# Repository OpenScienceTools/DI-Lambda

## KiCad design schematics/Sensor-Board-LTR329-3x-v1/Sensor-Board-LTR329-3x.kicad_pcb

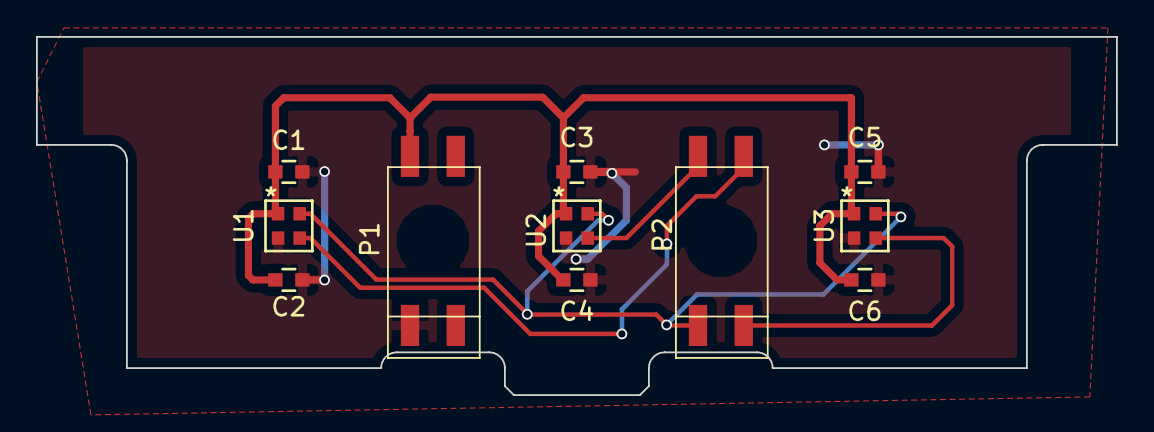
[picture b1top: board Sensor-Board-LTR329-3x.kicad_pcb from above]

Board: 2 copper layers, 60.0 x 19.9 mm, 11 parts (0 on the bottom side), 6 nets.

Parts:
C1, C3, C5: 22nF; C_0603
C2, C4, C6: 1uF; C_0603
P1, P2: CONN_02X02; SSM-102-X-DH
U1, U2, U3: LTR-329ALS-01; Liteon_ChipLED

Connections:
GND: C1.2, C2.2, C3.2, C4.2, C5.2, C6.2, P1.1, U1.2, U2.2, U3.2
SCL: P2.1, U1.4, U2.4, U3.4
SDA0: P2.4, U1.3
SDA1: P2.2, U2.3
SDA2: P2.3, U3.3
VDD: C1.1, C2.1, C3.1, C4.1, C5.1, C6.1, P1.2, U1.1, U2.1, U3.1

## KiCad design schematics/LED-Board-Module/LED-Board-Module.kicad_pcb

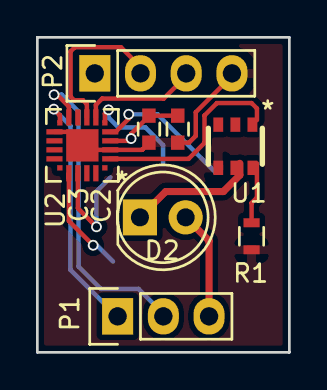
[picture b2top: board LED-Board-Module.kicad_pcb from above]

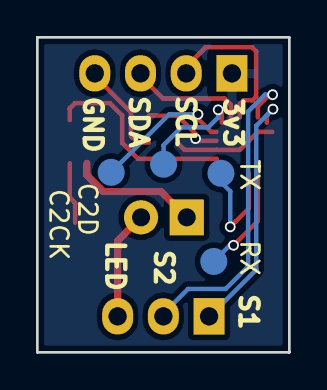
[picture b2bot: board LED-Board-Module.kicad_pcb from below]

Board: 2 copper layers, 14.0 x 17.5 mm, 12 parts (4 on the bottom side), 14 nets.

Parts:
C2: 1uF; C_0603
C3: 100nF; C_0603
D2: LED; LED-5MM
P1: CONN_01X03; Pin_Header_Straight_1x03
P2: CONN_01X04; Pin_Header_Straight_1x04
R1: 96R; R_0603
U1: BCR42XU; SOT26
U2: EFM8BB10F2G; Silabs-QFN20
W1: TX; TEST_POINT
W6: RX; TEST_POINT
W7: C2CK; TEST_POINT
W8: C2D; TEST_POINT

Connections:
CTRL: U1.1, U2.2
GND: C2.2, C3.2, P2.4, R1.1, U1.4, U2.3, U2.12, U2.21
LED: D2.2, P1.3
unnamed: D2.1, U1.5
unnamed: R1.2, U1.6
unnamed: U2.5, W7.1
unnamed: U2.6, W8.1
unnamed: U2.17, W6.1
unnamed: U2.18, W1.1
S1: P1.1, U2.11
S2: P1.2, U2.10
SCL: P2.2, U2.8
SDA: P2.3, U2.7
VDD: C2.1, C3.1, P2.1, U2.4

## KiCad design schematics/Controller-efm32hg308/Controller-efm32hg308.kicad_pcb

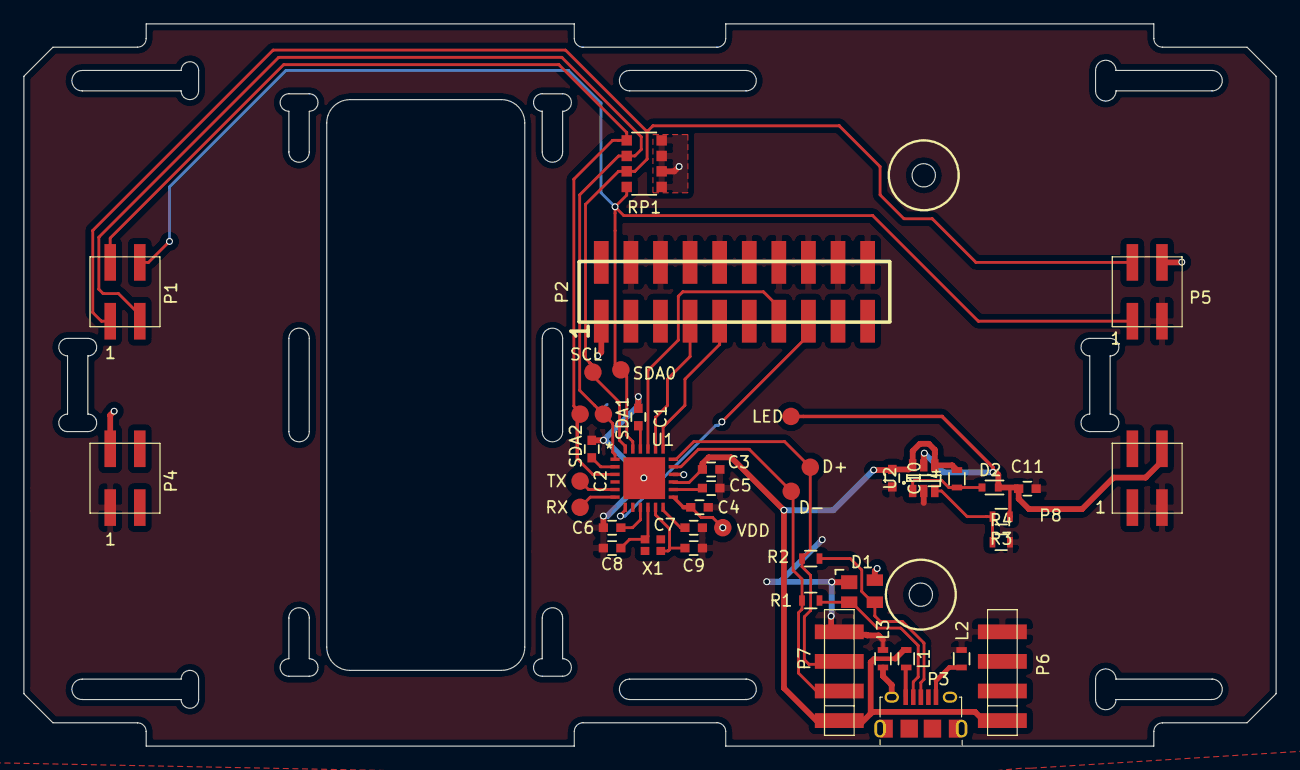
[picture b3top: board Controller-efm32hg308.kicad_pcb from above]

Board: 2 copper layers, 107.5 x 62.0 mm, 43 parts (0 on the bottom side), 30 nets.

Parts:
C1, C2, C6, C7: 100nF; C_0603
C3: 4.7uF; C_0603
C4, C5, C11: 1uF; C_0603
C8, C9: 6pF; C_0603
C10: 10uF; C_0603
D1: CM1293A-02SR; SOT-143
D2: D_Schottky; SOD-523
L1, L2, L3: FB; R_0603
L4: 6.8uH; R_0603
P1, P4, P5, P8: CONN_02X02; CONN_2x2_2.54_SMD
P2: CONN_02X10; SMD_PIN_HEADER_2x10
P3: USB_OTG; 10118194-001LF
P6, P7: CONN_01X04; SMT_CONN_01x04_2.54-91601
R1, R2: 15; R_0603
R3: 6.8K; R_0603
R4: 100R; R_0603
RP1: 4.7k; R_Array_Convex_4x1206
U1: EFM32HG308; Silabs-QFN24
U2: AP3023; SOT-23-6
W1: D+; TEST_POINT
W2: D-; TEST_POINT
W3: LED; TEST_POINT
W4: VDD; TEST_POINT
W5: SCL; TEST_POINT
W6: SDA0; TEST_POINT
W7: SDA1; TEST_POINT
W8: SDA2; TEST_POINT
W9: TX; TEST_POINT
W10: RX; TEST_POINT
X1: XRCGB_F_L

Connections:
D+: P7.3, R2.2, U1.18, W1.1
D-: P7.2, R1.2, U1.17, W2.1
GND: C1.1, C2.2, C3.1, C4.2, C5.2, C6.2, C7.2, C8.2, C9.2, C10.2, C11.2, D1.1, L2.1, L3.1, P2.4, P2.6, P2.8, P2.10, P2.12, P2.14, P2.16, P2.18, P2.20, P4.1, P5.3, P6.4, P7.4, P8.3, R4.2, U1.25, U2.2
LED: C11.1, D2.1, P8.4, R3.1, U2.5, W3.1
unnamed: C1.2, U1.22
unnamed: C2.1, U1.2
unnamed: C5.1, U1.14
unnamed: C6.1, U1.9
unnamed: C7.1, U1.12
unnamed: C8.1, U1.10, X1.1
unnamed: C9.1, U1.11, X1.3
unnamed: D1.2, P3.2, R1.1
unnamed: D1.3, P3.3, R2.1
unnamed: D2.2, L4.1, U2.1
unnamed: L1.1, P3.1
unnamed: L2.2, P3.5
unnamed: L3.2, P3.6
unnamed: P2.7, U1.20
unnamed: P2.9, U1.19
unnamed: P2.13, U1.21
unnamed: R3.2, R4.1, U2.3
unnamed: U1.5, W9.1
unnamed: U1.6, W10.1
RESETn: P2.15, U1.7
SCL: P1.1, P5.2, RP1.7, U1.24, W5.1
SDA0: P1.4, P5.1, RP1.8, U1.23, W6.1
SDA1: P1.3, RP1.6, U1.1, W7.1
SDA2: P1.2, RP1.5, U1.3, W8.1
VBUS: C3.2, C10.1, L1.2, L4.2, P6.1, P7.1, U1.15, U2.4, U2.6
VDD: C4.1, D1.4, P2.1, P4.2, P5.4, RP1.1, RP1.2, RP1.3, RP1.4, U1.13, U1.16, W4.1

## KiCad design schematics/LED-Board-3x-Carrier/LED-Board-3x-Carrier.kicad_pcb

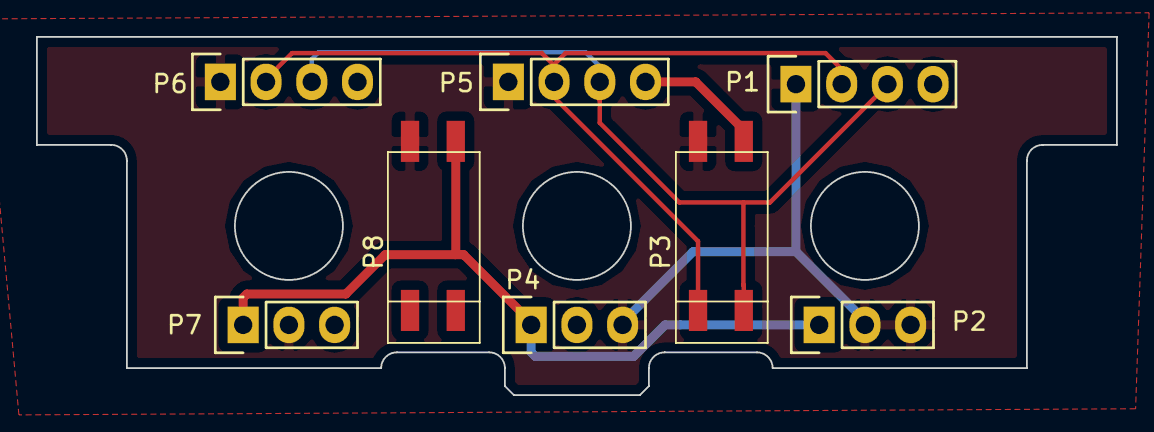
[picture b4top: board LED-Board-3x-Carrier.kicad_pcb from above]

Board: 2 copper layers, 60.0 x 19.9 mm, 8 parts (0 on the bottom side), 5 nets.

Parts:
P1, P5, P6: CONN_01X04; Socket_Strip_Straight_1x04
P2, P4, P7: CONN_01X03; Socket_Strip_Straight_1x03
P3, P8: CONN_02X02; SSM-102-X-DH

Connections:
GND: P1.1, P2.2, P2.3, P3.2, P4.3, P5.1, P6.1, P7.2, P8.2
LED: P2.1, P4.1, P7.1, P8.4
SCL: P1.3, P3.3, P5.3, P6.3
SDA: P1.2, P3.1, P5.2, P6.2
VDD: P1.4, P3.4, P4.2, P5.4, P6.4, P7.3

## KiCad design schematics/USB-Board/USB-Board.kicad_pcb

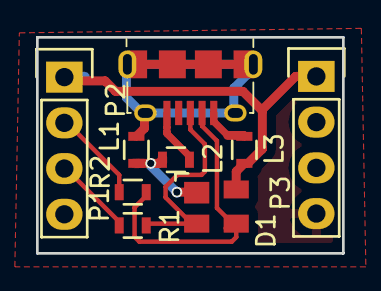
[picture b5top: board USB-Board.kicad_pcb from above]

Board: 2 copper layers, 17.0 x 12.0 mm, 9 parts (0 on the bottom side), 9 nets.

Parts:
D1: CM1293A-02SR; SOT-143
L1, L2, L3: FB; R_0603
P1, P3: CONN_01X04; Pin_Header_Straight_1x04
P2: USB_OTG; 10118194-001LF
R1, R2: 15; R_0603

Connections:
D+: P1.3, R1.2
D-: P1.2, R2.2
GND: D1.1, L1.1, L2.1, P1.4, P3.4
unnamed: D1.2, P2.3, R1.1
unnamed: D1.3, P2.2, R2.1
unnamed: L1.2, P2.6
unnamed: L2.2, P2.5
unnamed: L3.1, P2.1
VCC: D1.4, L3.2, P1.1, P3.1

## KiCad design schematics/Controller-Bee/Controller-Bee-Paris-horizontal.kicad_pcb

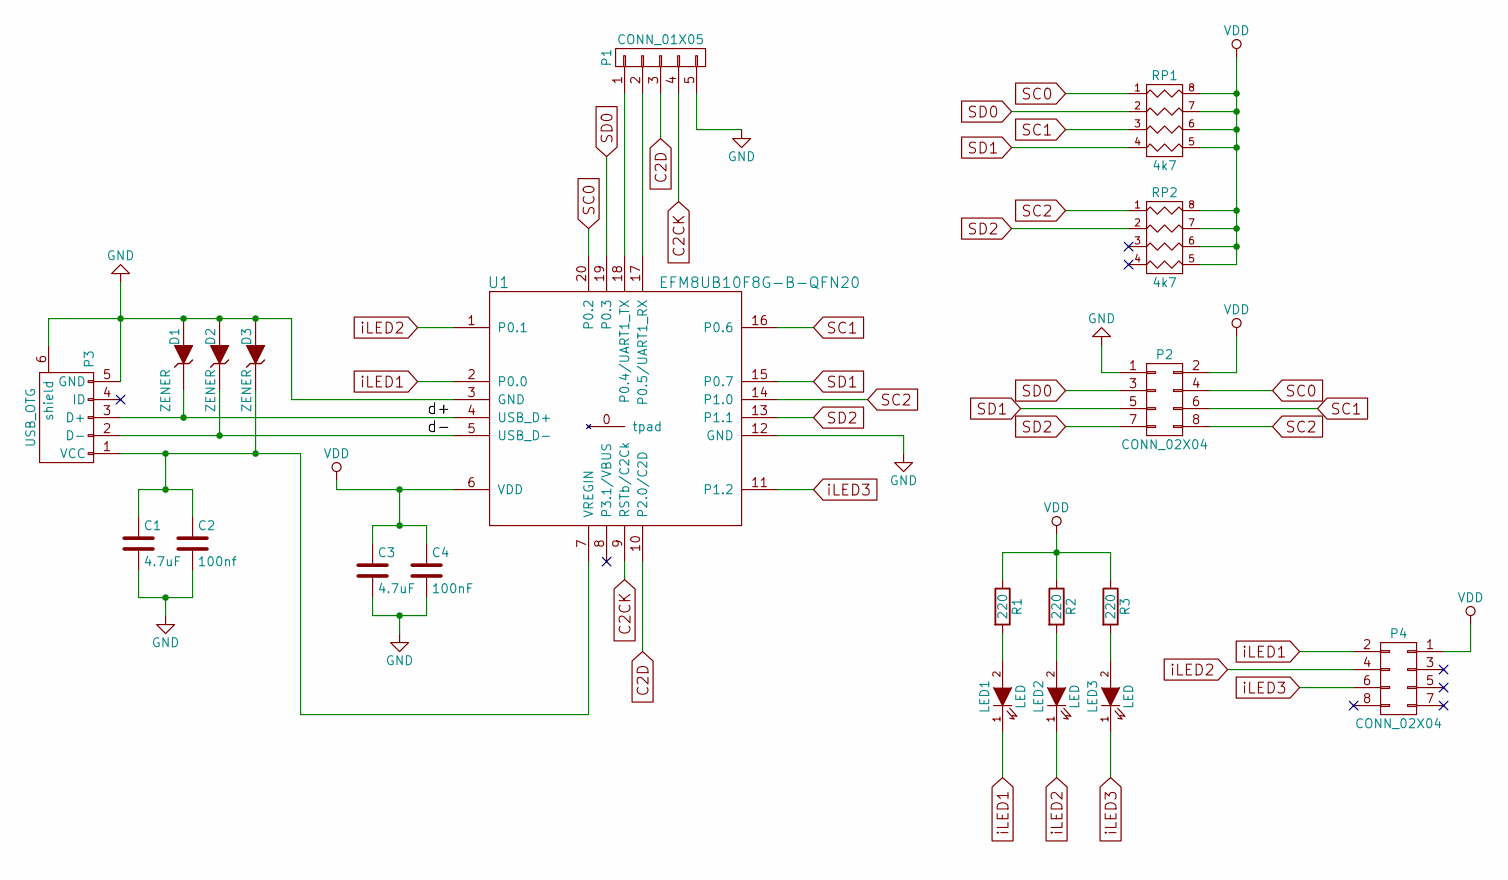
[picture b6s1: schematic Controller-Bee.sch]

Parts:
C1, C3: 4.7uF; C_0805
C2: 100nf; C_0805
C4: 100nF; C_0805
D1, D2, D3: ZENER; SMD-1206_Pol
LED1, LED2, LED3: LED; LED-5MM
P1: CONN_01X05; Pin_Header_Straight_1x05
P2, P4: CONN_02X04; Pin_Header_Straight_2x04_Pitch2.00mm
P3: USB_OTG; USB-B-mini
R1, R2, R3: 220; R_0805
RP1, RP2: 4k7; R_Array_Convex_4x0603
U1: EFM8UB10F8G-B-QFN20; Silabs-QFN20

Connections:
/d+: D1.1 (K), P3.3 (D+), U1.4 (USB_D+)
/d-: D2.1 (K), P3.2 (D-), U1.5 (USB_D-)
C2CK: P1.4, U1.9 (RSTb/C2Ck)
C2D: P1.3, U1.10 (P2.0/C2D)
GND: C1.2, C2.2, C3.2, C4.2, D1.2 (A), D2.2 (A), D3.2 (A), P1.5, P2.1, P3.5 (GND), P3.6 (shield), U1.3 (GND), U1.12 (GND)
unnamed: C1.1, C2.1, D3.1 (K), P3.1 (VCC), U1.7 (VREGIN)
unnamed: LED1.2 (A), R1.2
unnamed: LED2.2 (A), R2.2
unnamed: LED3.2 (A), R3.2
unnamed: P1.1, U1.18 (P0.4/UART1_TX)
unnamed: P1.2, U1.17 (P0.5/UART1_RX)
SC0: P2.4, RP1.1, U1.20 (P0.2)
SC1: P2.6, RP1.3, U1.16 (P0.6)
SC2: P2.8, RP2.1, U1.14 (P1.0)
SD0: P2.3, RP1.2, U1.19 (P0.3)
SD1: P2.5, RP1.4, U1.15 (P0.7)
SD2: P2.7, RP2.2, U1.13 (P1.1)
VDD: C3.1, C4.1, P2.2, P4.1, R1.1, R2.1, R3.1, RP1.5 (R4), RP1.6 (R3), RP1.7 (R2), RP1.8 (R1), RP2.5 (R4), RP2.6 (R3), RP2.7 (R2), RP2.8 (R1), U1.6 (VDD)
iLED1: LED1.1 (K), P4.2, U1.2 (P0.0)
iLED2: LED2.1 (K), P4.4, U1.1 (P0.1)
iLED3: LED3.1 (K), P4.6, U1.11 (P1.2)

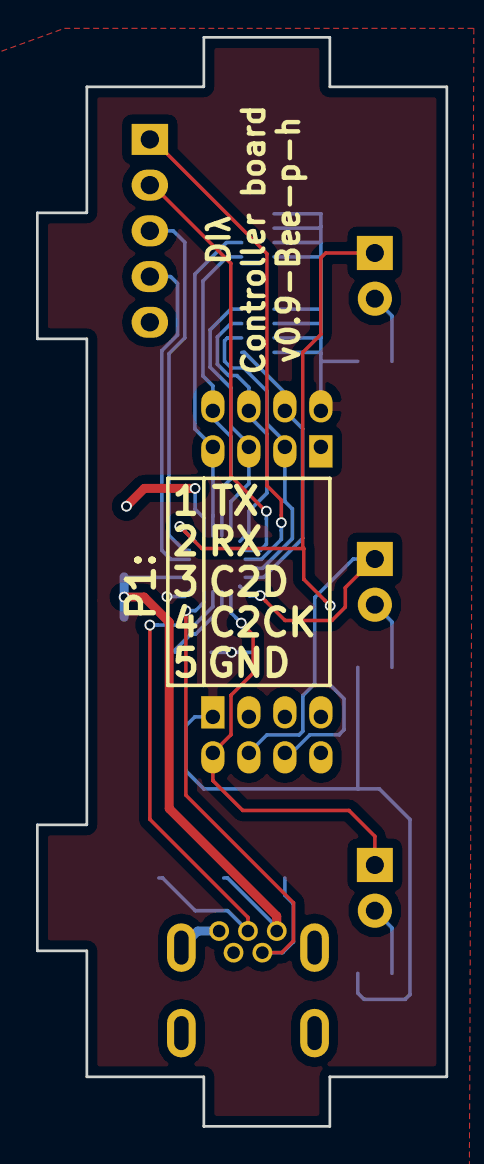
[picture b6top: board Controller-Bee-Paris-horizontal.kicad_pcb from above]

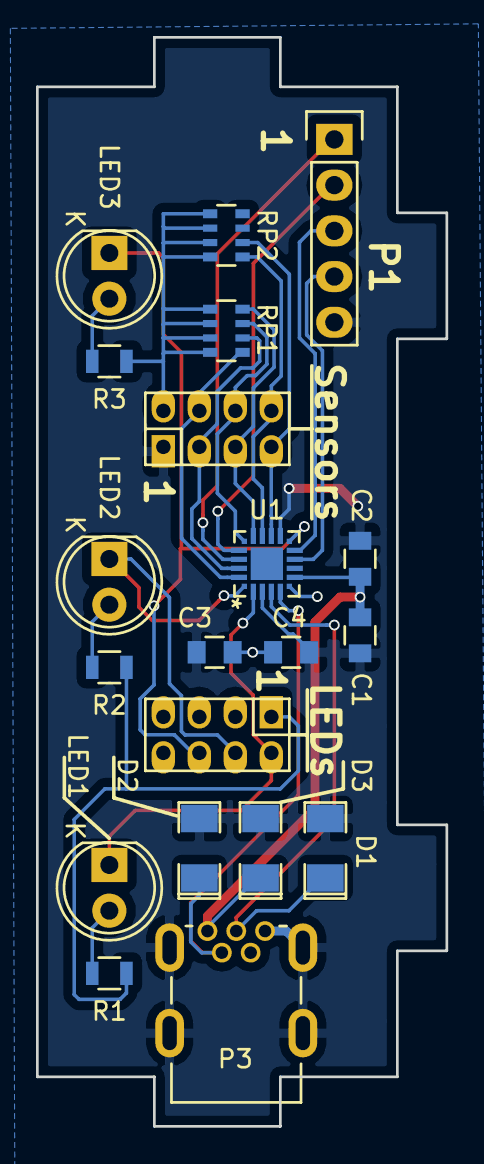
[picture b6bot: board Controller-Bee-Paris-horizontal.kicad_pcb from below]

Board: 2 copper layers, 22.8 x 60.5 mm, 20 parts (20 on the bottom side), 21 nets.

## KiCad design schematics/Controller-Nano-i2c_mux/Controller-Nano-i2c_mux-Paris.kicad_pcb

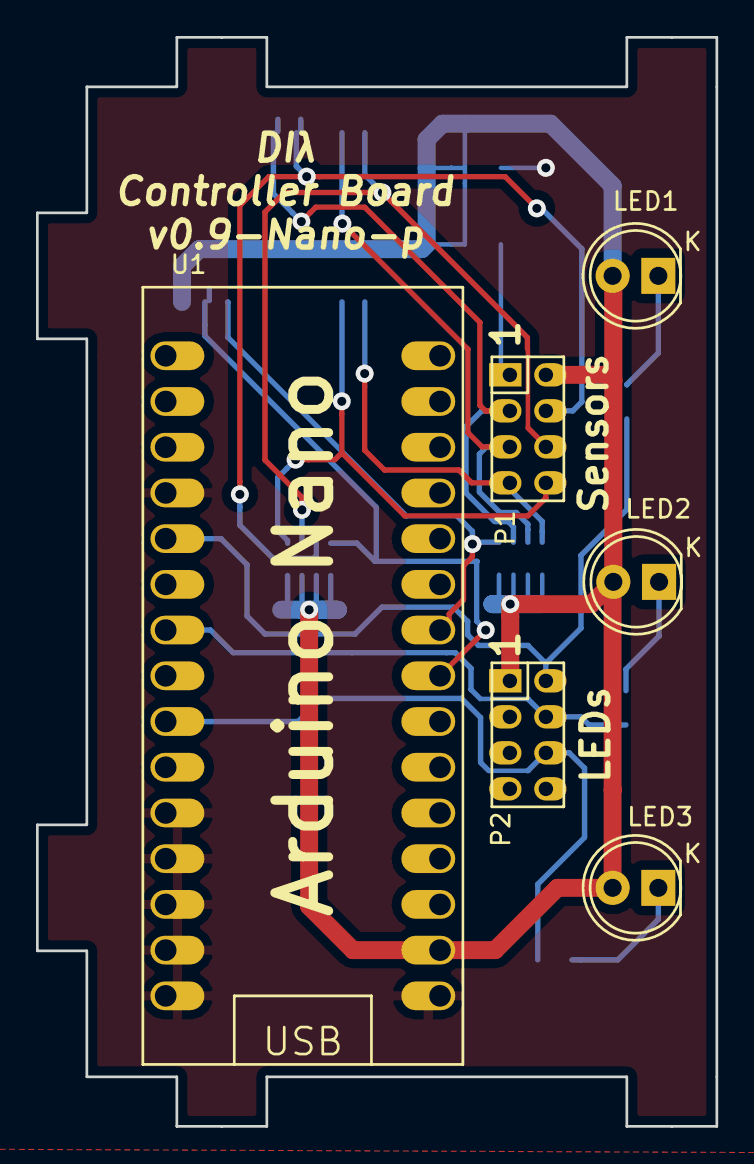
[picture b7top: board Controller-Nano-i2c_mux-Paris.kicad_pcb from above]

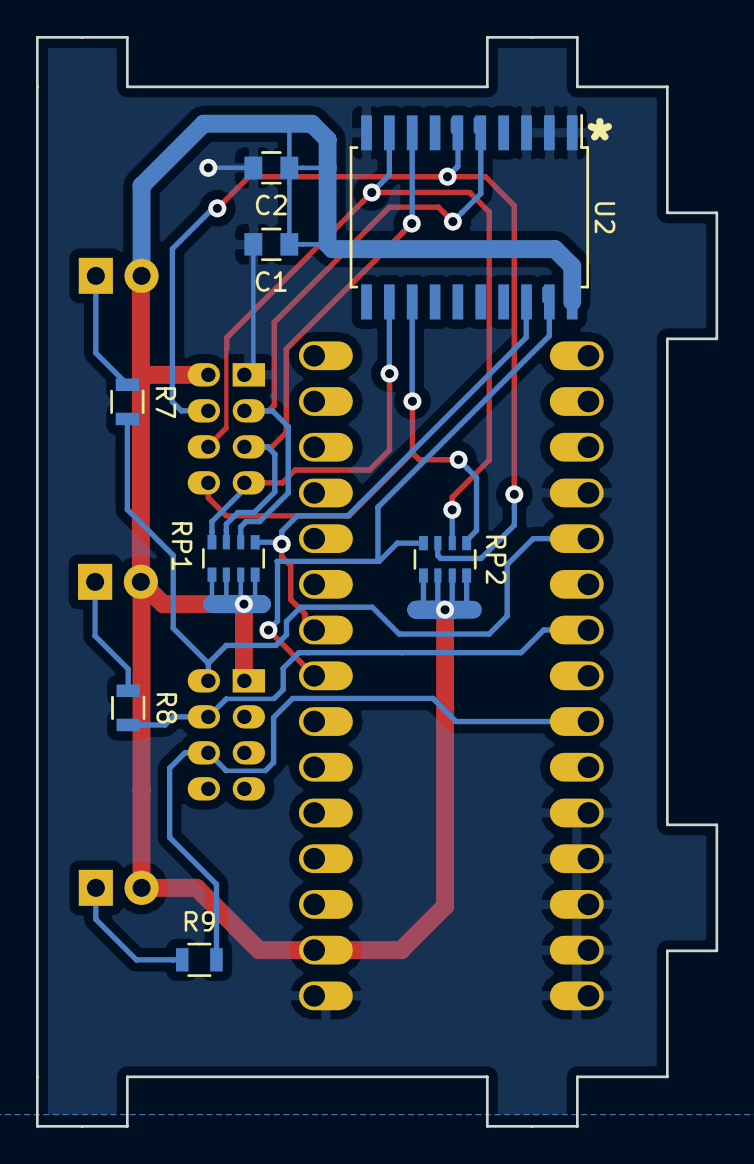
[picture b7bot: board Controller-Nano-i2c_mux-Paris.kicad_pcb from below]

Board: 2 copper layers, 37.8 x 60.5 mm, 14 parts (8 on the bottom side), 16 nets.

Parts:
C1: 22nF; C_0805
C2: 1uF; C_0805
LED1, LED2, LED3: LED; LED-5MM
P1, P2: CONN_02X04; Pin_Header_Straight_2x04_Pitch2.00mm
R7, R8, R9: 220; R_0805
RP1, RP2: R_PACK4; R_Array_Convex_4x0603
U1: Arduino_Nano; PDIP30-Nano
U2: PCA9544A; SOIC-20_7.5x12.8mm_Pitch1.27mm

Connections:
+3V3: C1.1, C2.1, LED1.2, LED2.2, LED3.2, P1.2, P2.1, RP1.5, RP1.6, RP1.7, RP1.8, RP2.5, RP2.6, RP2.7, RP2.8, U1.17, U2.20
GND: C1.2, C2.2, P1.1, U1.4, U1.11, U1.12, U1.13, U1.14, U1.15, U1.16, U2.1, U2.2, U2.3, U2.10
LED1: P2.2, R7.2, U1.5
LED2: P2.4, R8.2, U1.7
LED3: P2.6, R9.2, U1.9
unnamed: LED1.1, R7.1
unnamed: LED2.1, R8.1
unnamed: LED3.1, R9.1
SC0: P1.4, RP2.3, U2.6
SC1: P1.6, RP2.2, U2.9
SC2: P1.8, RP2.1, U2.13
SCL: RP1.1, U1.24, U2.18
SD0: P1.3, RP1.2, U2.5
SD1: P1.5, RP1.3, U2.8
SD2: P1.7, RP1.4, U2.12
SDA: RP2.4, U1.23, U2.19

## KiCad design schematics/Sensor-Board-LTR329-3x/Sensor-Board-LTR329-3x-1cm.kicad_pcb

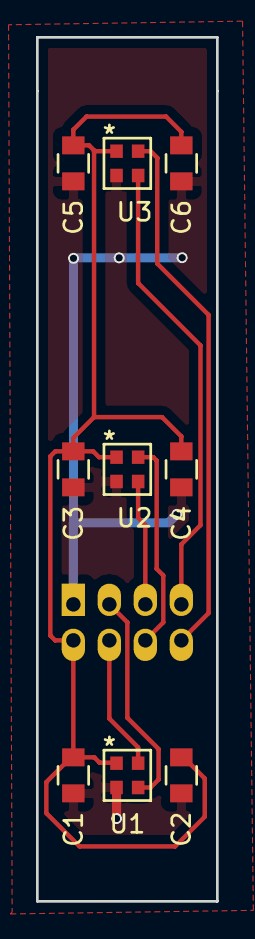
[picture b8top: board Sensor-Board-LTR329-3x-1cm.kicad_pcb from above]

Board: 2 copper layers, 10.0 x 48.0 mm, 10 parts (1 on the bottom side), 8 nets.

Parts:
C1, C2, C3, C4, C5, C6: C; C_0805
P1: CONN_02X04; Pin_Header_Straight_2x04_Pitch2.00mm
U1, U2, U3: LTR-329ALS-01; Liteon_ChipLED

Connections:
+3V3: C1.1, C2.1, C3.1, C4.1, C5.1, C6.1, P1.2, U1.1, U2.1, U3.1
GND: C1.2, C2.2, C3.2, C4.2, C5.2, C6.2, P1.1, U1.2, U2.2, U3.2
SC0: P1.4, U1.4
SC1: P1.6, U2.4
SC2: P1.8, U3.4
SD0: P1.3, U1.3
SD1: P1.5, U2.3
SD2: P1.7, U3.3

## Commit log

2014-12-25 Some unfinished schematics
2014-12-25 Add some unfinished parts
2014-12-25 Finish up the fist version, excluding the top part
2014-12-25 Render assembly
2014-12-25 Some progress with schematics
2014-12-25 Add stl exports for 3d printing
2014-12-25 Add pdf files for preview
2014-12-25 Add the top part of the box
2014-12-25 Some updates
2014-12-30 More detailed leds on the lead board
2014-12-30 Second version base part
2014-12-30 Second version of the top part
2014-12-30 stl export for the second version top part
2014-12-30 Add cuvette model
2014-12-31 Smaller motherboard, dimension changes to allow some gap betwen parts
2014-12-31 Add motherboard sketch to Render
2014-12-31 Add the cover part
2014-12-31 Accomodate top part for the cover
2014-12-31 Some changes here and there
2014-12-31 Some changes
2015-01-06 Reworked some schematics
2015-01-06 Rework bottom part to optimize size
2015-01-06 Bottom part sketch
2015-01-07 Actually add the base drender
2015-01-07 Finish the size rework
2015-01-11 Add assembly render pictures
2015-01-13 A last-minute commit before leaving for Grenoble
2015-02-03 New partially laser-cut version
2015-02-03 Add the laser-cut Autocad parts
2015-02-03 Just a quick fix
2015-06-03 Add the test rig, lots of other changes
2015-06-03 Spirulina prototype
2015-06-12 Start with the new slim design
2015-06-16 Some changes to parts used in the London event
2015-06-16 Add the distance test rig base
2015-06-16 Convert laser-cut parts to AI
2015-06-24 DI-Lambda Paris
2015-06-24 Align things to verify board dimensions
2015-06-29 DIL-Paris takes shape
2015-07-14 DI-Lambda Luna
2015-07-19 Steps towards a screwless case for DI-Lambda Paris
2015-07-19 Large git repo cleanup - move files around, remove unused
2015-07-19 Large git repo cleanup - update assemblies
2015-07-20 Spirulina: Add missing 1mm slit
2015-07-20 Paris: First attempt on screwless box
2015-07-21 Clean up the screwless box design
2015-08-01 Update screwless box design and rework the controller board
2015-08-05 Assemblies for each device, to make nice pictures
2015-08-07 Remove old schematics
2015-08-15 New slit inserts for the test rig
2015-08-19 All new schematics and boards
    - Reworked with KiCad
    - Includes:
    -- 2 Microcontroller board with Arduino Nano
    -- Microcontroller board with the Silabs EFM8UB10F8G MCU
    -- 1cm LED board
    -- 1cm sensor board with TSL2561
2015-08-20 schematics: update LED connections, use 4x resistor arrays
2016-03-11 Large amount of random changes
2016-05-24 Update the DI-Lambda Paris design: PCB pinholes, easier board removal, larger cuvette holes
2016-05-24 Add missing files for the nice-looking DI-Lambd Paris v2 version (cancelled)
2016-05-24 Add DI-Lambda v1 based on SZOMK AK-C-C10 profile (cancelled)
2016-05-24 Add DI-Lambda v1 based on SZOMK AK-C-C39 profile
2016-05-24 Schematics update
2016-05-24 DI-Lambda Paris: Fix core and box mismatches
2016-05-24 Schamatics: Add the pinhole board KiCad files
2016-07-03 Electronics update for V1
2016-07-03 Update V1 mechanical parts
